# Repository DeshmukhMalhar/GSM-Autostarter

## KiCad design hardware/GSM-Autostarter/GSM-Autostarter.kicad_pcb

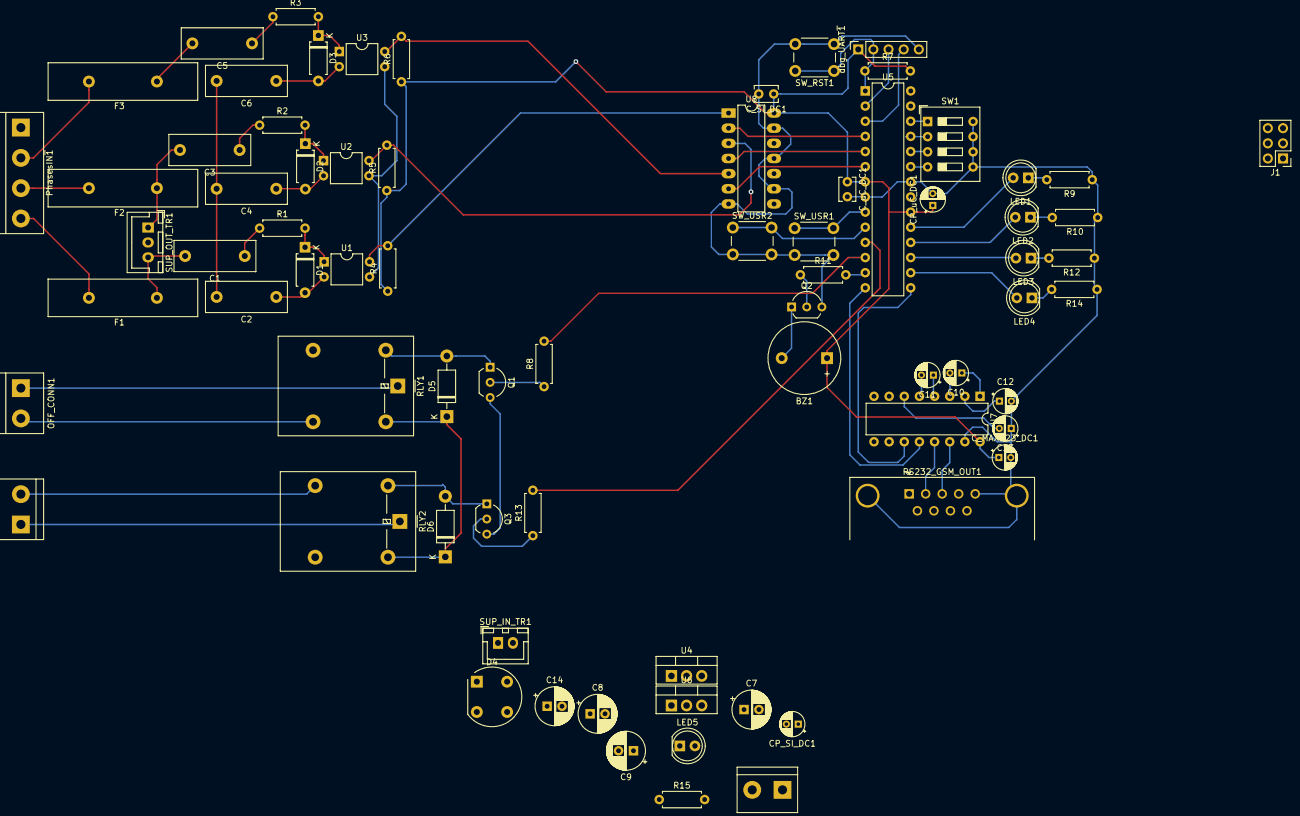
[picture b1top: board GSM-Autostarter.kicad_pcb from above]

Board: 2 copper layers, 75 parts (0 on the bottom side), 69 nets.

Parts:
BZ1: Buzzer; Buzzer_12x9.5RM7.6
C1, C2, C3, C4, C5, C6: 100n/400v POLY; C_Rect_L13.5mm_W5.0mm_P10.00mm_FKS3_FKP3_MKS4
C7, C8, C9: 47u/50v; CP_Radial_D6.3mm_P2.50mm
C10, C11, C12, C13: 1u/25v; CP_Radial_D4.0mm_P2.00mm
C14: 220u/50v; CP_Radial_D6.3mm_P2.50mm
CP_SI_DC1: 1u/25v; CP_Radial_D4.0mm_P2.00mm
CP_uC_DC1: 1u/25v; CP_Radial_D4.0mm_P2.00mm
C_MAX323_DC1: 1u/25v; CP_Radial_D4.0mm_P2.00mm
C_SI_DC1: 0u1/ceramic; C_Disc_D3.8mm_W2.6mm_P2.50mm
C_uC_DC1: 0u1/ceramic; C_Disc_D3.8mm_W2.6mm_P2.50mm
D1, D2, D3: 3v6; D_A-405_P7.62mm_Horizontal
D4: W10G; Diode_Bridge_Round_D9.8mm
D5, D6: 1N4007; D_DO-41_SOD81_P10.16mm_Horizontal
F1, F2, F3: 600v/1A polyfuse; Fuse_Littelfuse-LVR200
GSM_PWR_OUT1: 2PIN_Phoenix Conn; TerminalBlock_bornier-2_P5.08mm
J1: AVR-ISP-6; PinHeader_2x03_P2.54mm_Vertical
LED1: LED_5mm_YELLOW; LED_D5.0mm
LED2, LED4: LED_5mm_GREEN; LED_D5.0mm
LED3, LED5: LED_5mm_RED; LED_D5.0mm
OFF_CONN1: 2PIN_Phoenix Conn; TerminalBlock_bornier-2_P5.08mm
ON_CONN1: 2PIN_Phoenix Conn; TerminalBlock_bornier-2_P5.08mm
PhasesIN~1: 4 PIN_Phoenix Conn; TerminalBlock_bornier-4_P5.08mm
Q1, Q2, Q3: BC547; TO-92_Inline_Wide
R1: 10K/1W; R_Axial_DIN0207_L6.3mm_D2.5mm_P7.62mm_Horizontal
R2, R3, R7: 10K; R_Axial_DIN0207_L6.3mm_D2.5mm_P7.62mm_Horizontal
R4, R5, R6, R8, R9, R10, R11, R12, R13, R14, R15: 330; R_Axial_DIN0207_L6.3mm_D2.5mm_P7.62mm_Horizontal
RLY1, RLY2: 9V_coil/250V|7A (RAS-0910); Relay_SPDT_Omron-G5LE-1
RS232_GSM_OUT1: DB9_Male_PCBMOUNT; DSUB-9_Male_Horizontal_P2.77x2.84mm_EdgePinOffset4.94mm_Hou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
SUP_IN_TR1: Relimate 2 pin; JST_XH_B02B-XH-A_1x02_P2.50mm_Vertical
SUP_OUT_TR1: Relimate 3 pin; JST_XH_B03B-XH-A_1x03_P2.50mm_Vertical
SW1: SW_DIP_x04; SW_DIP_SPSTx04_Slide_9.78x12.34mm_W7.62mm_P2.54mm
SW_RST1: MX3; SW_PUSH_6mm_H5mm
SW_USR1, SW_USR2: MX3; SW_PUSH_6mm_H5mm
U1, U2, U3: PC817; DIP-4_W7.62mm
U4: LM7809_TO220; TO-220-3_Vertical
U5: ATmega328P-PU; DIP-28_W7.62mm
U6: LM1117-3.3; TO-220-3_Vertical
U7: MAX232; DIP-16_W7.62mm
U8: 74HC14; DIP-14_W7.62mm_LongPads
dbg_UART~1: DNP; PinSocket_1x05_P2.54mm_Vertical

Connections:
/+9V: C8.1, D5.1, D6.1, GSM_PWR_OUT1.1, RLY1.5, RLY2.5, U4.3, U6.3
/GSM_RX_H: RS232_GSM_OUT1.2, U7.13
/GSM_RX_L: U5.14, U7.12
/GSM_TX_H: RS232_GSM_OUT1.3, U7.14
/GSM_TX_L: U5.15, U7.11
/MISO: J1.1, LED2.2, U5.18
/MOSI: J1.4, LED3.2, U5.17
/SCK: J1.3, LED1.2, U5.19
/U: C1.2, F1.1, SUP_OUT_TR1.3
/U_LOW: U5.4, U8.2
/V: C3.2, F2.1, SUP_OUT_TR1.1
/V_LOW: U5.5, U8.4
/W: C5.2, F3.1
/W_LOW: U5.6, U8.6
/dbg_RX_L: U5.2, dbg_UART~1.3
/dbg_TX_L: U5.3, dbg_UART~1.4
/rly_OFF: R8.2, U5.12
/rly_ON: R13.2, U5.11
/~RST: J1.5, R7.1, SW_RST1.1, U5.1, dbg_UART~1.2
Earth: C2.2, C4.2, C6.2, PhasesIN~1.1
GNDD: C7.2, C8.2, C9.2, C12.2, C13.1, C14.2, CP_SI_DC1.2, CP_uC_DC1.2, C_MAX323_DC1.2, C_SI_DC1.2, C_uC_DC1.2, D4.3, GSM_PWR_OUT1.2, J1.6, Q1.3, Q2.3, Q3.3, R9.1, R10.1, R12.1, R14.1, R15.1, RS232_GSM_OUT1.0, RS232_GSM_OUT1.5, SW1.5, SW1.6, SW1.7, SW1.8, SW_RST1.2, SW_USR1.2, SW_USR2.2, U1.3, U2.3, U3.3, U4.2, U5.8, U5.22, U6.1, U7.15, U8.7, U8.9, U8.11, U8.13, dbg_UART~1.5
unnamed: BZ1.2, Q2.1
unnamed: C1.1, R1.1
unnamed: C2.1, D1.2, U1.2
unnamed: C3.1, R2.1
unnamed: C4.1, D2.2, U2.2
unnamed: C5.1, R3.1
unnamed: C6.1, D3.2, U3.2
unnamed: C10.1, U7.1
unnamed: C10.2, U7.3
unnamed: C11.1, U7.4
unnamed: C11.2, U7.5
unnamed: C12.1, U7.2
unnamed: C13.2, U7.6
unnamed: D1.1, R1.2, U1.1
unnamed: D2.1, R2.2, U2.1
unnamed: D3.1, R3.2, U3.1
unnamed: D4.2, SUP_IN_TR1.2
unnamed: D4.4, SUP_IN_TR1.1
unnamed: D5.2, Q1.1, RLY1.2
unnamed: D6.2, Q3.1, RLY2.2
unnamed: F1.2, PhasesIN~1.4
unnamed: F2.2, PhasesIN~1.3
unnamed: F3.2, PhasesIN~1.2
unnamed: LED1.1, R9.2
unnamed: LED2.1, R10.2
unnamed: LED3.1, R12.2
unnamed: LED4.1, R14.2
unnamed: LED4.2, U5.16
unnamed: LED5.1, R15.2
unnamed: OFF_CONN1.1, RLY1.1
unnamed: OFF_CONN1.2, RLY1.4
unnamed: ON_CONN1.1, RLY2.1
unnamed: ON_CONN1.2, RLY2.3
unnamed: Q1.2, R8.1
unnamed: Q2.2, R11.1
unnamed: Q3.2, R13.1
unnamed: R4.2, U1.4, U8.1
unnamed: R5.2, U2.4, U8.3
unnamed: R6.2, U3.4, U8.5
unnamed: R11.2, U5.13
unnamed: SW1.1, U5.26
unnamed: SW1.2, U5.25
unnamed: SW1.3, U5.24
unnamed: SW1.4, U5.23
unnamed: SW_USR1.1, U5.9
unnamed: SW_USR2.1, U5.10
VCC: C7.1, C14.1, D4.1, U4.1
VDD: BZ1.1, C9.1, CP_SI_DC1.1, CP_uC_DC1.1, C_MAX323_DC1.1, C_SI_DC1.1, C_uC_DC1.1, J1.2, LED5.2, R4.1, R5.1, R6.1, R7.2, U5.7, U5.20, U6.2, U7.16, U8.14, dbg_UART~1.1

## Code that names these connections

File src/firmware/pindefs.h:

#define pindefs_h
#define SWREVISION "0.0.1"
#define dbg_rx 0
#define dbg_tx 1
#define u_in 2
#define v_in 3
#define w_in 4
#define rly_ON 5
#define rly_OFF 6
#define BUZZ 7
#define gsm_RX_L 8
#define gsm_TX_L 9
#define LED_GREEN 10
#define LED_RED 11
#define LED_GREEN2 12
#define LED 13
#define IN_POT A5
#define USR_SW1 20
#define USR_SW2 21

#define CONFIG (PINC & 0x0f) //reads config DIPsw and masks it

#define OUT(X) pinMode(X, OUTPUT)
#define IN(X) pinMode(X, INPUT)
#define IN_PU(X) pinMode(X, INPUT_PULLUP)

#define read(X) digitalRead(X)

#define ON(X) digitalWrite(X, 1)
#define OFF(X) digitalWrite(X, 0)

#define DEL_TIME_STD 6600
#define RELAY_HOLD 500
#define ERROR -1
#define GOOD 2

#define ERROR_FLASH_DLY 50
#define GOOD_FLASH_DLY 100
enum config_states
{
	NO_GSM_actualDelay = 0,
	NO_GSM_twiceDelay,
	GSM_actualDelay,
	GSM_twiceDelay,

	SETUP = 0x0a,

};

const String about = String("GSM-Autostarter \n") + String("Firmware Version: ") + String(SWREVISION) + String("\n") + String("BUILT on\n") + String(__DATE__) + String("\n") + String(__TIME__);

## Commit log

2018-12-08 pindefs complete
2018-12-08 add .gitignore
2018-12-08 schematic verification pending
2018-12-08 update .gitignore for kicad files
2018-12-08 add 74HC14 and user input switches
2018-12-08 user switch defines added
2018-12-09 basic test 3 phase detection
2018-12-09 add condition on Pin change interrupt fot trig only on LOW
2018-12-09 updated upto pcb
2018-12-09 testing phase shifts
2018-12-09 started phase detection
2018-12-10 intermidiate steps to phase detection
2018-12-10 timediff 3 phases good
2018-12-11 update gitignore exclude vscode /output/
2018-12-11 gitignore .vscode
2018-12-11 upadates according to kanban board
2018-12-11 offline start under test
2018-12-11 exclude *.json
